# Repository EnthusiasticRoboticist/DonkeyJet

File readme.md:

# Workspace for DonkeyJet [Under ACTIVE CONSTRUCTION]

Introducing my ongoing robotics project, currently named **DonkeyJet**, inspired by the [Donkey Car project](https://www.donkeycar.com/). This mobile robot is built on an RC car frame and powered by Jetson Nano, providing a hands-on platform for practicing robotics knowledge. The goal is to continually enhance its capabilities while exploring various aspects of robotics technology. While I am not certain about the name DonkeyJet, I invite you to follow me on this exciting journey of discovery as I document my progress and share insights with fellow enthusiasts in my weblog [here](https://www.enthusiasticroboticist.com/).

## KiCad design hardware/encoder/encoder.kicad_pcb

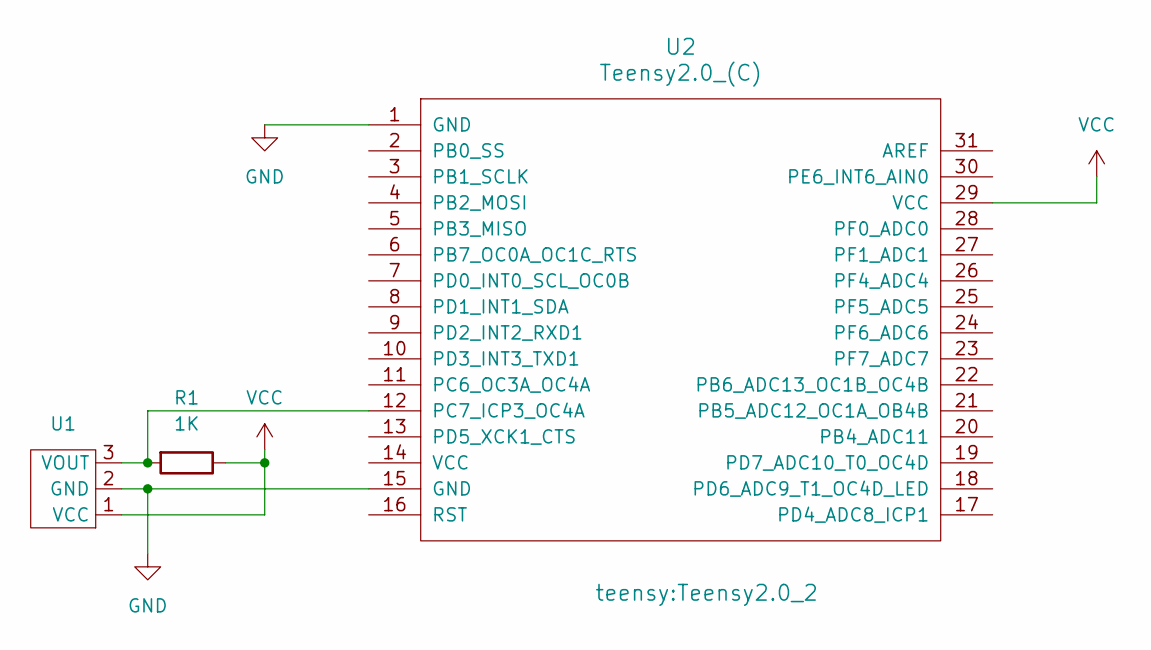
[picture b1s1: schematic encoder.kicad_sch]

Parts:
R1: 1K; R_Axial_DIN0207_L6.3mm_D2.5mm_P7.62mm_Horizontal
U1: ATS668LSM_1
U2: Teensy2.0_(C); Teensy2.0_2

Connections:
GND: U1.2 (GND), U2.1 (GND), U2.15 (GND)
unnamed: R1.2, U1.3 (VOUT), U2.12 (PC7_ICP3_OC4A)
VCC: R1.1, U1.1 (VCC), U2.29 (VCC)

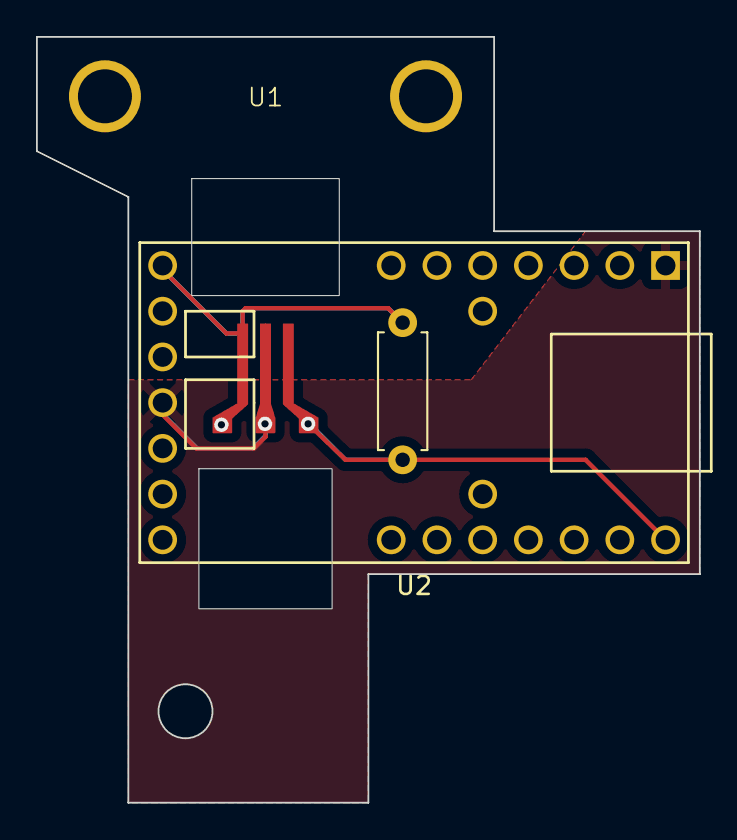
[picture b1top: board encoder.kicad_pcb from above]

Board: 2 copper layers, 36.8 x 42.5 mm, 3 parts (0 on the bottom side), 3 nets.

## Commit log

2023-03-21 using a launch file instead of running multiple nodes on different terminals
2023-03-29 fixing issues with cuda inside the containers
2023-04-05 a docker image that works
2023-04-06 ros realsense is working on jetson with cuda support
2023-05-02 [Hardware][WIP] reading IMU and publishing odom
    - basic node that publishes IMU message type from nav_msgs package.
    - links to realsense SKD and read IMU from realsesne.
    - Swapped the D435i with D435
    - Unit test works, receiving imu from T265 and depth from D435
2023-05-08 Setup the development environment for the my realsense wrapper development
2023-05-14 [realsense] the realsense base node works consistently
2023-05-14 - Added a new message "Control" that has throttle and steering values - Added a new node to convert the Joy messages to Control messages - Change the Joy and PCA nodes to accomodate these changes.
2023-05-18 rtabmap inside the docker file with foxy
2023-05-20 clean up for realsense image
    Update readme.md
2023-07-15 Files related to the Gear tooth Sensor as Encoder for DonkeyJet
